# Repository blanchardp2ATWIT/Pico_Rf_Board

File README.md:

# Pico_Rf_Board
Buncha Rf amateurs trying to figure this out. 

https://www.digikey.com/en/products/detail/pulse-electronics/ANT1204LL20R0433A/9360390
https://www.digikey.com/en/products/detail/johanson-technology-inc/0433AT62A0020001E/4770690
https://www.te.com/usa-en/product-ANT-433-SP.datasheet.pdf
https://www.digikey.com/en/products/detail/linx-technologies-inc/ANT-433-USP410/13165345
https://www.digikey.com/en/products/detail/abracon-llc/ACAG1204-433-T/8593245

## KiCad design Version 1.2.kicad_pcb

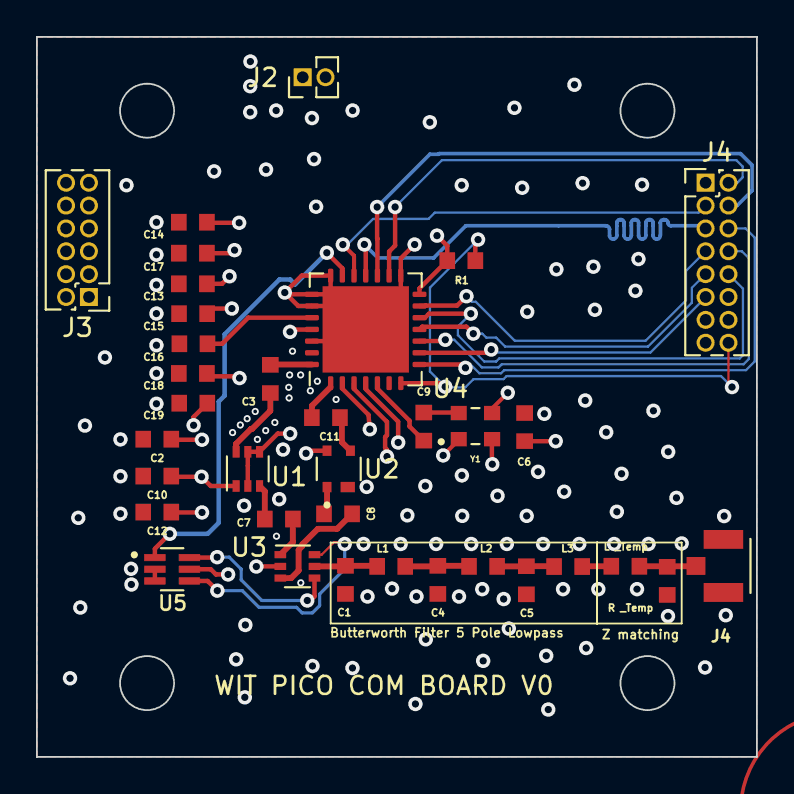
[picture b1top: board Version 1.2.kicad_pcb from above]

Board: 4 copper layers, 40.0 x 40.0 mm, 35 parts (0 on the bottom side), 35 nets.

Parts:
C1, C5: 2.236 pF; RESC1608X55N
C2: 50 pF; RESC1608X55N
C3, C8, C11: 100 pF; RESC1608X55N
C4: 7.234 pF; RESC1608X55N
C6: .1 Uf; RESC1608X55N
C7: 22 nF; RESC1608X55N
C9: 15 pF; RESC1608X55N
C10: 10 nF; RESC1608X55N
C12, C13, C15, C17, C19: 100 nF; RESC1608X55N
C14, C16, C18: 10 uF; RESC1608X55N
J2: Conn_01x02_Pin; PinHeader_1x02_P1.27mm_Vertical
J3: Conn_01x12_Socket; PinHeader_2x06_P1.27mm_Vertical
J4: Conn_01x16_Socket; PinHeader_2x08_P1.27mm_Vertical
J4#2: Conn_Coaxial; TE_1909763-1
L1, L2: 14.632 nH; RESC1608X55N
L3: 3.9 nH; RESC1608X55N
L _Temp: 3.9 nH; RESC1608X55N
R1, R1#2: 4.7k; RESC1608X55N
U1: BGA2801; SOT-363_SC-70-6
U2: BGA420; INFINEON_BFP540
U3: AS179-92LF; SOT-363_SC-70-6
U4: SX1278; QFN-28-1EP_6x6mm_P0.65mm_EP4.8x4.8mm
U5: 74LVC1G19; SOT65P210X110-6N
Y1: ECS-TXO-2520-33-400-AN-TR; OSC_ECS-TXO-2520-33-400-AN-TR

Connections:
+3.3V: C2.2, C6.1, C10.1, C12.1, C14.1, C17.1, C19.1, J2.2, J3.12, J4.12, R1.1, U1.1 (Vcc), U2.4 (VD), U4.14 (VBAT_DIG), U4.25 (VR_PA), U5.5 (VCC), Y1.1 (GND), Y1.4 (TRI-STATE)
/Antenna_Control: U4.20 (RXTX/RF_MOD), U5.1 (A)
/DECODER_OUT_1: U3.4 (V1), U5.6 (Y0)
/DECODER_OUT_2: U3.6 (V2), U5.4 (Y1)
/DIO_0: J4.6, U4.8 (DIO0)
/DIO_1: J4.11, U4.9 (DIO1)
/DIO_2: J4.8, U4.10 (DIO2)
/DIO_3: J4.9, U4.11 (DIO3)
/DIO_4: J4.10, U4.12 (DIO4)
/DIO_5: J4.7, U4.13 (DIO5)
/Filter_Input: C1.1, L1.1, U3.5 (J1)
/Filter_Output: L3.2, L _Temp.1
/LNA_INPUT: C8.1, U3.3 (J2)
/LNA_OUTPUT: C11.2, U4.1 (RFI_LF)
/MISO: J4.4, U4.17 (MISO)
/MOSI: J4.5, U4.18 (MOSI)
/NSS: J4.3, U4.19 (NSS)
/PA_Input: C3.1, U4.28 (RFO_LF)
/PA_OUTPUT: C7.2, U3.1 (J3)
/Reset: J4.16, R1.2, U4.7 (~RESET)
/SCK: J4.2, U4.16 (SCK)
/TCXO_OUT: C9.2, Y1.3 (VDD)
GND: C1.2, C2.1, C4.2, C5.2, C6.2, C10.2, C12.2, C13.2, C14.2, C15.2, C16.2, C17.2, C18.2, C19.2, J2.1, J3.1, J4.1, J4#2.2 (Ext), J4#2.3 (Ext), R1#2.1, U1.2 (G), U1.4 (G), U1.5 (G), U2.2 (GND), U3.2 (GND), U4.15 (GND), U4.21 (RFI_HF), U4.22 (RFO_HF), U4.23 (GND), U4.26 (GND), U4.29 (GND), U5.2 (GND), U5.3 (~E), Y1.2 (OUTPUT)
unnamed: C3.2, U1.6
unnamed: C4.1, L1.2, L2.1
unnamed: C5.1, L2.2, L3.1
unnamed: C7.1, U1.3
unnamed: C8.2, U2.1 (IN)
unnamed: C11.1, U2.3 (OUT)
unnamed: C18.1, U4.3 (VBAT_ANA)
unnamed: C16.1, U4.24 (VBAT_RF)
unnamed: C15.1, U4.2 (VR_ANA)
unnamed: C13.1, U4.4 (VR_DIG)
unnamed: C9.1, U4.5 (XTA)
temp: J4#2.1 (In), L _Temp.2, R1#2.2

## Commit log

2023-07-18 Initial Commit - Test
2023-07-18 Fixed RF Line. Made Components closer together to improve impedance matching, straightened RF Path to reduce electron collision.
2023-07-18 Forgot to Fill Lol
2023-07-18 Fixed Footprints nothing changed in grand scheme of things. Just for clarity sake.
2023-07-18 EMI & Compression
2023-07-18 Ants
2023-07-18 Fixed signal lines In preparation for EMI Shielding.
2023-07-19 Small Updates
2023-07-25 Added a version with and without solder voids.
2023-07-28 Final Rev 1.0
2023-08-01 Ordered Version
2023-09-14 Fix Clock Pads
2023-09-17 Fixed Clock and LNA
